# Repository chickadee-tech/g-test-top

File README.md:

# Chickadee Tech Generic Test Jig Top #
This is the top board to the generic test jig for Polystack **control** and **mod** boards.

## Documentation ##
See the [wiki](https://github.com/chickadee-tech/g-test-top/wiki) for documentation.

## Polystack ##
This board is part of the Polystack platform for modular microcontrol systems. More information on the platform can be found at [polystack.org](http://polystack.org).

## Support ##
If you need support with a board you own or have development questions please email support@chickadee.tech or check [chickadee.tech/support](https://chickadee.tech/support) for other ways to get support.

## Contributing ##
Please note that this project is released with a [Contributor Code of Conduct](CODE_OF_CONDUCT.md). By participating in this project you agree to abide by its terms.

### Setup ###
Components and footprints for PCB parts are not included in this repository. Instead, checkout the [chickadee-tech/kicad-libs](https://github.com/chickadee-tech/kicad-libs) repository in the same directory that this repository is checked out in. All part definitions should be relative so that they will load correctly.

### Pull requests ###
For fixes please submit a pull request to the original repository. After the pull request is merged, check the [Chickadee Tech Active Contributor Discount (ACD)](https://chickadee.tech/active-contributor) to see if you are eligible for a discount code to use on your next purchase.

### Derivatives ###
If developing your own version of the test jig top please remove all Chickadee Tech trademarks and follow the [CC-BY license](LICENSE). While not required, please consider open sourcing your modifications so others can learn from your improvements. If you do email support@chickadee.tech and we may choose to add your project to the ACD.

You may also license the Polystack logo for free by emailing support@chickadee.tech. We'll ask for your gerbers to ensure the design complies with specifications laid out [here](https://github.com/chickadee-tech/polystack/wiki) and provide written permission to use the trademark after compliance has been demonstrated.

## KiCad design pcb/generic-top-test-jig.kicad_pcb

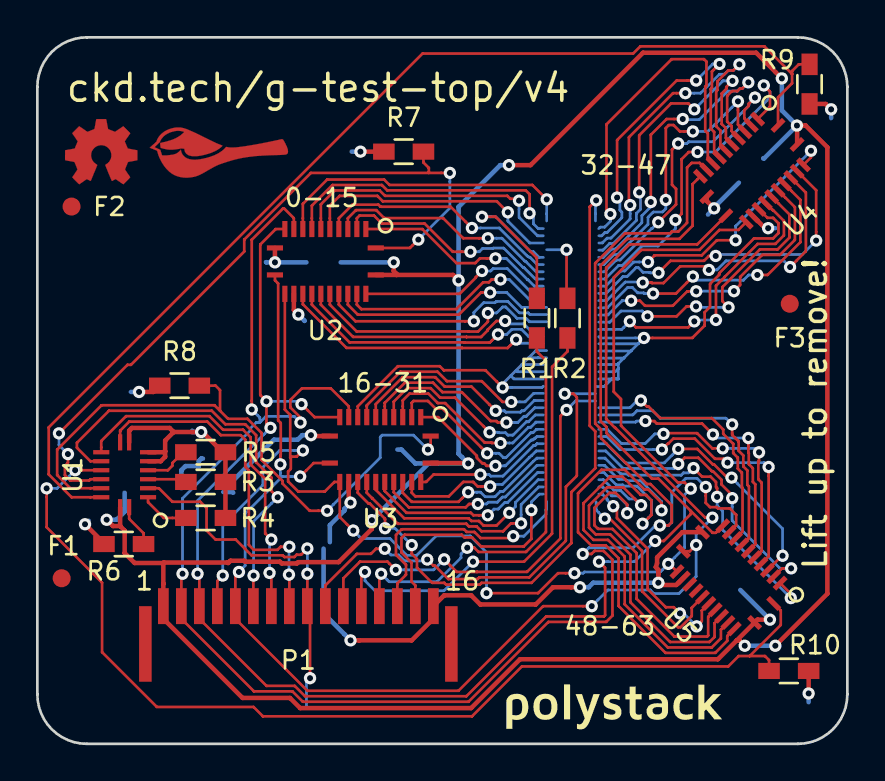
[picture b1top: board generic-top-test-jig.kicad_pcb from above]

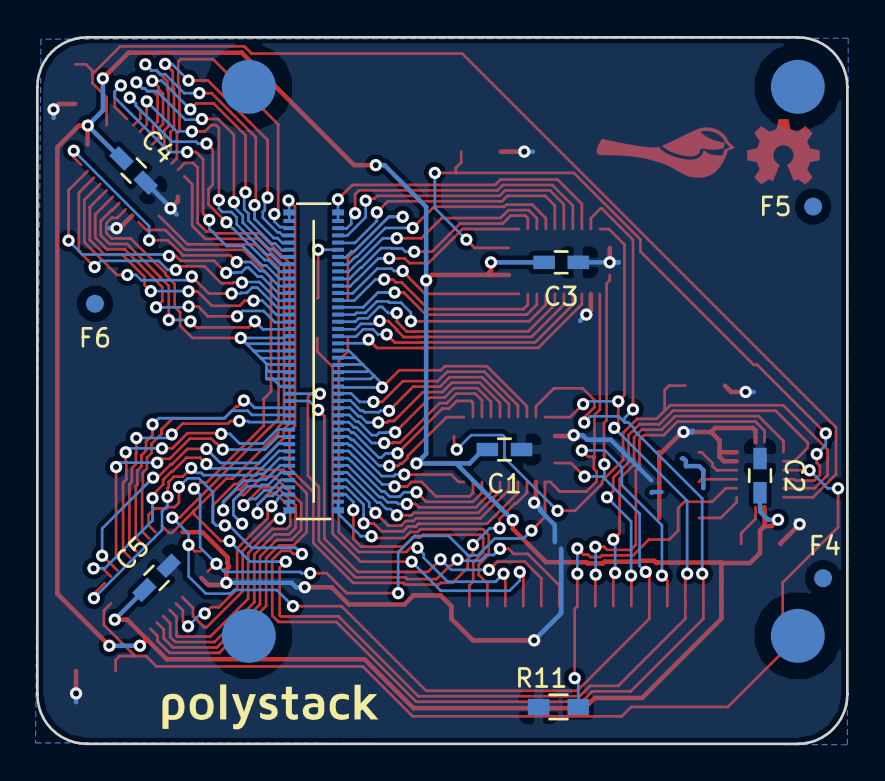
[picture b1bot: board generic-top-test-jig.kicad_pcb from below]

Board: 2 copper layers, 45.0 x 39.2 mm, 31 parts (11 on the bottom side), 88 nets.

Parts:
C1, C2, C3, C4, C5: 0.1uF; C_0603_HandSoldering
F1, F2, F3, F4, F5, F6: 1mm; Fiducial
P1: CONN_01X16; SFW12LF-16pin
PORT_IN1: CKD_SANDWICH; DF40-80pin-Header
R1, R2: 220; R_0603_HandSoldering
R3, R4, R5, R6, R7, R8, R9, R10, R11: 10k; R_0603_HandSoldering
U1: 74HC4051; SOT763-1(DHVQFN16)
U2, U3, U4, U5: 74HC4067; DHVQFN24
svg2mod, svg2mod#2: G***; polystack-bold-0.625

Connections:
+5V: C1.2, C2.2, C3.2, C4.1, C5.1, P1.1, U1.16, U2.24, U3.24, U4.24, U5.24
/3V3_0.3A_E: PORT_IN1.17, U2.17
/3V3_0.3A_LL: PORT_IN1.16, U2.18
/5V: PORT_IN1.19, PORT_IN1.20, PORT_IN1.21, PORT_IN1.22, PORT_IN1.23, PORT_IN1.24, U3.9
/+BATT: PORT_IN1.18, U2.16
/ADC1: PORT_IN1.49, U4.2
/ADC2: PORT_IN1.50, U4.23
/BOOT: P1.10, PORT_IN1.65
/CAN_HI: PORT_IN1.67, U5.9
/CAN_LO: PORT_IN1.68, U5.8
/GND: PORT_IN1.57, PORT_IN1.58, PORT_IN1.59, PORT_IN1.60, PORT_IN1.61, PORT_IN1.62, PORT_IN1.63, PORT_IN1.64, U4.16
/GPIO3: PORT_IN1.7, U2.5
/GPIO4: PORT_IN1.8, U2.4
/GPIO5: PORT_IN1.9, U2.3
/GPIO6: PORT_IN1.10, U2.2
/HEIGHT_1: PORT_IN1.15, U2.19
/HEIGHT_2: PORT_IN1.14, U2.20
/HEIGHT_4: PORT_IN1.13, U2.21
/RESET: P1.11, PORT_IN1.66
/RX: P1.14, PORT_IN1.40
/S0: P1.2, U2.10, U3.10, U4.10, U5.10
/S1: P1.3, U2.11, U3.11, U4.11, U5.11
/S2: P1.4, U2.14, U3.14, U4.14, U5.14
/S3: P1.5, U2.13, U3.13, U4.13, U5.13
/S4: P1.6, U1.11
/S5: P1.7, U1.10
/S6: P1.8, U1.9
/SDMMC1_CK: PORT_IN1.55, U4.18
/SDMMC1_CMD: PORT_IN1.56, U4.17
/SDMMC1_D0: PORT_IN1.51, U4.22
/SDMMC1_D1: PORT_IN1.52, U4.21
/SDMMC1_D2: PORT_IN1.53, U4.20
/SDMMC1_D3: PORT_IN1.54, U4.19
/SPI1_MISO: PORT_IN1.79, U5.19
/SPI1_MOSI: PORT_IN1.80, U5.18
/SPI1_NSS: PORT_IN1.77, U5.21
/SPI1_SCK: PORT_IN1.78, U5.20
/SPI2_MISO: PORT_IN1.75, U5.23
/SPI2_MOSI: PORT_IN1.76, U5.22
/SPI2_NSS: PORT_IN1.73, U5.3
/SPI2_SCK: PORT_IN1.74, U5.2
/SPI3_MISO: PORT_IN1.71, U5.5
/SPI3_MOSI: PORT_IN1.72, U5.4
/SPI3_NSS: PORT_IN1.69, U5.7
/SPI3_SCK: PORT_IN1.70, U5.6
/SWCLK: PORT_IN1.6, R1.2
/SWDIO: PORT_IN1.5, R2.2
/TIM1: PORT_IN1.1, U2.9
/TIM2: PORT_IN1.2, U2.8
/TIM3: PORT_IN1.3, U2.7
/TIM4: PORT_IN1.4, U2.6
/TIMG1_CH1: PORT_IN1.41, U3.16
/TIMG1_CH2: PORT_IN1.42, U4.9
/TIMG1_CH3: PORT_IN1.43, U4.8
/TIMG1_CH4: PORT_IN1.44, U4.7
/TIMG2_CH1: PORT_IN1.45, U4.6
/TIMG2_CH2: PORT_IN1.46, U4.5
/TIMG2_CH3: PORT_IN1.47, U4.4
/TIMG2_CH4: PORT_IN1.48, U4.3
/TX: P1.15, PORT_IN1.39
/UART2_RX: PORT_IN1.38, U3.17
/UART2_TX: PORT_IN1.37, U3.18
/UART3_RX: PORT_IN1.36, U3.19
/UART3_TX: PORT_IN1.35, U3.20
/UART4_RX: PORT_IN1.34, U3.21
/UART4_TX: PORT_IN1.33, U3.22
/UART5_RX: PORT_IN1.32, U3.23
/UART5_TX: PORT_IN1.31, U3.2
/UART6_RX: PORT_IN1.30, U3.3
/UART6_TX: PORT_IN1.29, U3.4
/UART7_RX: PORT_IN1.28, U3.5
/UART7_TX: PORT_IN1.27, U3.6
/UART8_RX: PORT_IN1.26, U3.7
/UART8_TX: PORT_IN1.25, U3.8
/Z: P1.9, R11.2, U1.3
/Z0: R7.2, U1.13, U2.1
/Z1: R8.2, U1.14, U3.1
/Z2: R9.2, U1.15, U4.1
/Z3: R10.2, U1.12, U5.1
/i2c_SCL: PORT_IN1.12, U2.22
/i2c_SDA: PORT_IN1.11, U2.23
GNDPWR: C1.1, C2.1, C3.1, C4.2, C5.2, P1.16, R3.1, R4.1, R5.1, R6.1, R7.1, R8.1, R9.1, R10.1, R11.1, U1.6, U1.7, U1.8, U2.12, U2.15, U3.12, U3.15, U4.12, U4.15, U5.12, U5.15
unnamed: P1.12, R2.1
unnamed: P1.13, R1.1
unnamed: R3.2, U1.4
unnamed: R4.2, U1.2
unnamed: R5.2, U1.5
unnamed: R6.2, U1.1

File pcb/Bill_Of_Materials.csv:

part name,symbol,size (imp),max current,unit price,units per build,units in stock,order total,Manufacturer ID,source url,datasheet,datasheet2,,,
80 pin header,PORT_IN1,,,$1.35,1,1,$1.35,DF40C-80DP-0.4V(51),http://www.digikey.com/product-detail/en/DF40C-80DP-0.4V(51)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,N,http://www.hirose.co.jp/cataloge_hp/ed_DF40_20140305.pdf,,Total Base Cost,$7.13
side entry bottom 16pos 1mm,P1,,,$0.92,1,0,$0.92,SFW16R-3STE1LF,http://www.digikey.com/product-detail/en/SFW16R-3STE1LF/609-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,N,,price ranges 1.40 - 2.50,,
1x8 mux,U1,16-VFQFN Exposed Pad,,$0.43,1,1,$0.43,"74HC4051BQ,115","http://www.digikey.com/product-detail/en/74HC4051BQ,115/568-7741-1-ND/2753885",N,http://www.nxp.com/documents/data_sheet/74HC_HCT4051.pdf,,,
1x16 mux,"U2, U3, U4, U5",24-VFQFN Exposed Pad,,$1.06,4,0,$4.26,"74HC4067BQ,118","http://www.digikey.com/product-detail/en/74HC4067BQ,118/568-8885-1-ND/2813803",N,http://www.nxp.com/documents/data_sheet/74HC_HCT4067.pdf,,,
~3.5mm Spacer,Off Board,,,$0.08,1,81,$0.08,908-140,http://www.mouser.com/search/ProductDetail.aspx?R=0virtualke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,N,http://www.bivar.com/Portals/0/Products/d.ashx?f=/Portals/0/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,,,
R 220,"R1, R2",603,,$0.00,2,493,$0.01,RC0603JR-07220RL,http://www.digikey.com/product-detail/en/yageo/RC0603JR-0722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,MF-RES-0603-220,http://www.yageo.com/NewPortal/yageodocoutput?fileName=/pdf/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,,,
R 10k,"R3, R4, R5, R6, R7, R8, R9, R10, R11",603,,$0.01,9,979,$0.09,RC0603FR-0710KL,http://www.digikey.com/product-detail/en/RC0603FR-0710KL/311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,MF-RES-0603-10K,http://www.yageo.com/NewPortal/yageodocoutput?fileName=/pdf/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,,,

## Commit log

2016-01-26 Top board of test jig.
2016-01-30 Gerbers for v1 of the test jig.
2016-03-05 Generic Test Jig Top v2 which correct Vee input in 8-way mux and changes SWD pins.
    Also:
    * Switches to thinner FlightStack logo.
    * Adds OSHW logo.
2016-04-07 Add decoupling caps.
2016-04-13 Rebrand everything to Polystack and increment versions.
2016-04-16 Final gerbers for test manufacturing run.
2016-06-07 Update polystack logo to bold variant and bump version number.
2016-07-07 Add license information to many files. PCB design files are CC-BY and code is MIT license.
2016-07-07 Add back .gitignore after repo split.
2016-07-07 Convert to relative component and footprint paths.

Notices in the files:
pcb/generic-top-test-jig.kicad_pcb:
Copyright 2016 Chickadee Tech LLC,
This work is licensed under the Creative Commons Attribution 4.0 International License.
To view a copy of this license, visit http://creativecommons.org/licenses/by/4.0
or send a letter to Creative Commons, PO Box 1866, Mountain View, CA 94042, USA.
